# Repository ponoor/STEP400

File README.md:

# STEP400

STEP400 is a 4-axis stepper motor driver board with an Ethernet interface, designed for art installations, stage productions and exhibition machinery. It puts everything a typical motion setup needs onto one board:

- An Arduino Zero–compatible MCU (Microchip ATSAMD21G18A)
- Ethernet (WIZnet W5500)
- Four [STMicroelectronics powerSTEP01](https://www.st.com/en/motor-drivers/powerstep01.html) stepper drivers, supporting both voltage mode and current mode
- HOME and LIMIT sensor inputs for each axis
- A microSD card slot for loading the configuration file

The board is controlled with [Open Sound Control](https://opensoundcontrol.stanford.edu/) (OSC) over Ethernet, which works natively in Max, TouchDesigner, Processing, openFrameworks, Unity and other creative coding environments.

| | |
|---|---|
| Motor type | Bipolar stepper |
| Supply voltage | 12–72 V (absolute max. 80 V) |
| Max. phase current | 5 A |
| Microstepping | Up to 1/128 |
| PCB size | 120 × 84 mm |

STEP400 is part of the STEP series. Its sibling, [STEP800](https://github.com/ponoor/STEP800), drives eight smaller motors with L6470 drivers and shares the same firmware and OSC commands.

Friend of STEP400 : [STEP800](https://github.com/ponoor/STEP800)

## Store
https://ponoor.com/en/shop/

## Documentation
https://ponoor.com/en/docs/step-series/

Forum: https://github.com/ponoor/step-series-support/discussions

- **[STEP400/STEP800 documentation](https://ponoor.com/en/docs/step-series/)** ([日本語](https://ponoor.com/docs/step-series/))
  - [Tutorial](https://ponoor.com/en/docs/step-series/tutorial/)
  - [OSC command reference](https://ponoor.com/en/docs/step-series/osc-command-reference/)
  - [Hardware details](https://ponoor.com/en/docs/step-series/technical-information/hardware-step400/)
- [Electromagnetic brake board for STEP400](https://ponoor.com/en/docs/emb-step400/)
- Questions and support: [STEP series support forum](https://github.com/ponoor/step-series-support/discussions)

## Firmware

The firmware is maintained in a separate repository, shared with STEP800:

**[ponoor/step-series-universal-firmware](https://github.com/ponoor/step-series-universal-firmware)**

This repository used to contain the STEP400 firmware as well. Those directories have been removed, and the old releases here are no longer maintained. See [Firmware update](https://ponoor.com/en/docs/step-series/technical-information/firmware-update/) in the documentation for how to update a board.

## Repository contents

### `hardware/`

Design files for the current hardware revision (r1).

| File | Description |
|---|---|
| `step400_r1.sch`, `step400_r1.brd` | STEP400 r1 schematic and board (Autodesk EAGLE). These are the reference design files for r1. |
| `step400_r1_schematics.pdf` | STEP400 r1 schematic |
| `step400_r1_dimension.pdf` | Board dimensions and mounting holes |
| `step400_r1.0.1_BOM.csv` | Bill of materials for r1.0.1 (current) |
| `step400_r1.0.0_BOM.csv` | Bill of materials for r1.0.0 |
| `brakeBoard.sch`, `brakeBoard.brd` | Electromagnetic brake board (Autodesk EAGLE) |
| `brakeBoard_schematic.pdf`, `brakeBoard_BOM.csv` | Brake board schematic and bill of materials |
| `step400_r1/` | KiCad project imported from the EAGLE r1 files (see below) |

#### KiCad migration (work in progress)

We are moving the hardware design from EAGLE to KiCad for the next revision. `hardware/step400_r1/` holds the r1 design imported into KiCad 10, along with a footprint library (`step400_r1.pretty`) exported from the board.

The connectivity and footprints of this KiCad project have been checked against the EAGLE files. However, it is kept as a **reference for future work**, not as manufacturing data. The PCB still carries leftovers from the import (an unconsolidated layer stack, missing keepout areas, default design rules), so use the EAGLE files or the PDFs above if you need the exact r1 design.

### `configTool/`

Source of the web-based configuration tool, which creates the JSON configuration file that the board loads from its microSD card. A hosted version is available at [ponoor.com/tools/step400-config/](https://ponoor.com/tools/step400-config/). For usage, see [Setup with a microSD card](https://ponoor.com/en/docs/step-series/settings/setup-with-a-microsd-card/).

### `step400_hardware_tests/`

A PlatformIO project for the hardware inspection firmware, used to test assembled boards.

## Examples and libraries

| Environment | Repository |
|---|---|
| Max | [ponoor/step-series-example-Max](https://github.com/ponoor/step-series-example-Max) |
| TouchDesigner | [ponoor/step-series-example-TouchDesigner](https://github.com/ponoor/step-series-example-TouchDesigner) (by [@loveandsheep](https://github.com/loveandsheep)) |
| openFrameworks | [ponoor/step-series-example-openFrameworks](https://github.com/ponoor/step-series-example-openFrameworks) (by [@niimi](https://github.com/niimi)) |
| Unity | [ponoor/step-series-example-Unity](https://github.com/ponoor/step-series-example-Unity) (by [@niimi](https://github.com/niimi)) |
| Processing | [yuskegoto/STEP400_Processing](https://github.com/yuskegoto/STEP400_Processing) (by [@yuskegoto](https://github.com/yuskegoto)) |
| Node-RED | [yuskegoto/STEP400_Node-RED](https://github.com/yuskegoto/STEP400_Node-RED) (by [@yuskegoto](https://github.com/yuskegoto)) |
| Python | [ponoor/python-step-series](https://github.com/ponoor/python-step-series) |

## License

[MIT License](LICENSE) © Ponoor Experiments Inc.

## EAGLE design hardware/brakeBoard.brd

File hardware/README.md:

# Diagram
```mermaid
flowchart LR
	MCU ---|SPI/SERCOM4| W5500 --- Ethernet
	MCU --- |SPI/SERCOM3|PowerSTEP01 --> Motor
	HomeSw -->|SW| PowerSTEP01
	LimitSw -->|ADCIN| PowerSTEP01
	DIPSW --> MCU
	MCU --> Brake
  ```
  
  Check the [document](https://ponoor.com/en/docs/step-series/technical-information/hardware-step400/) for details.

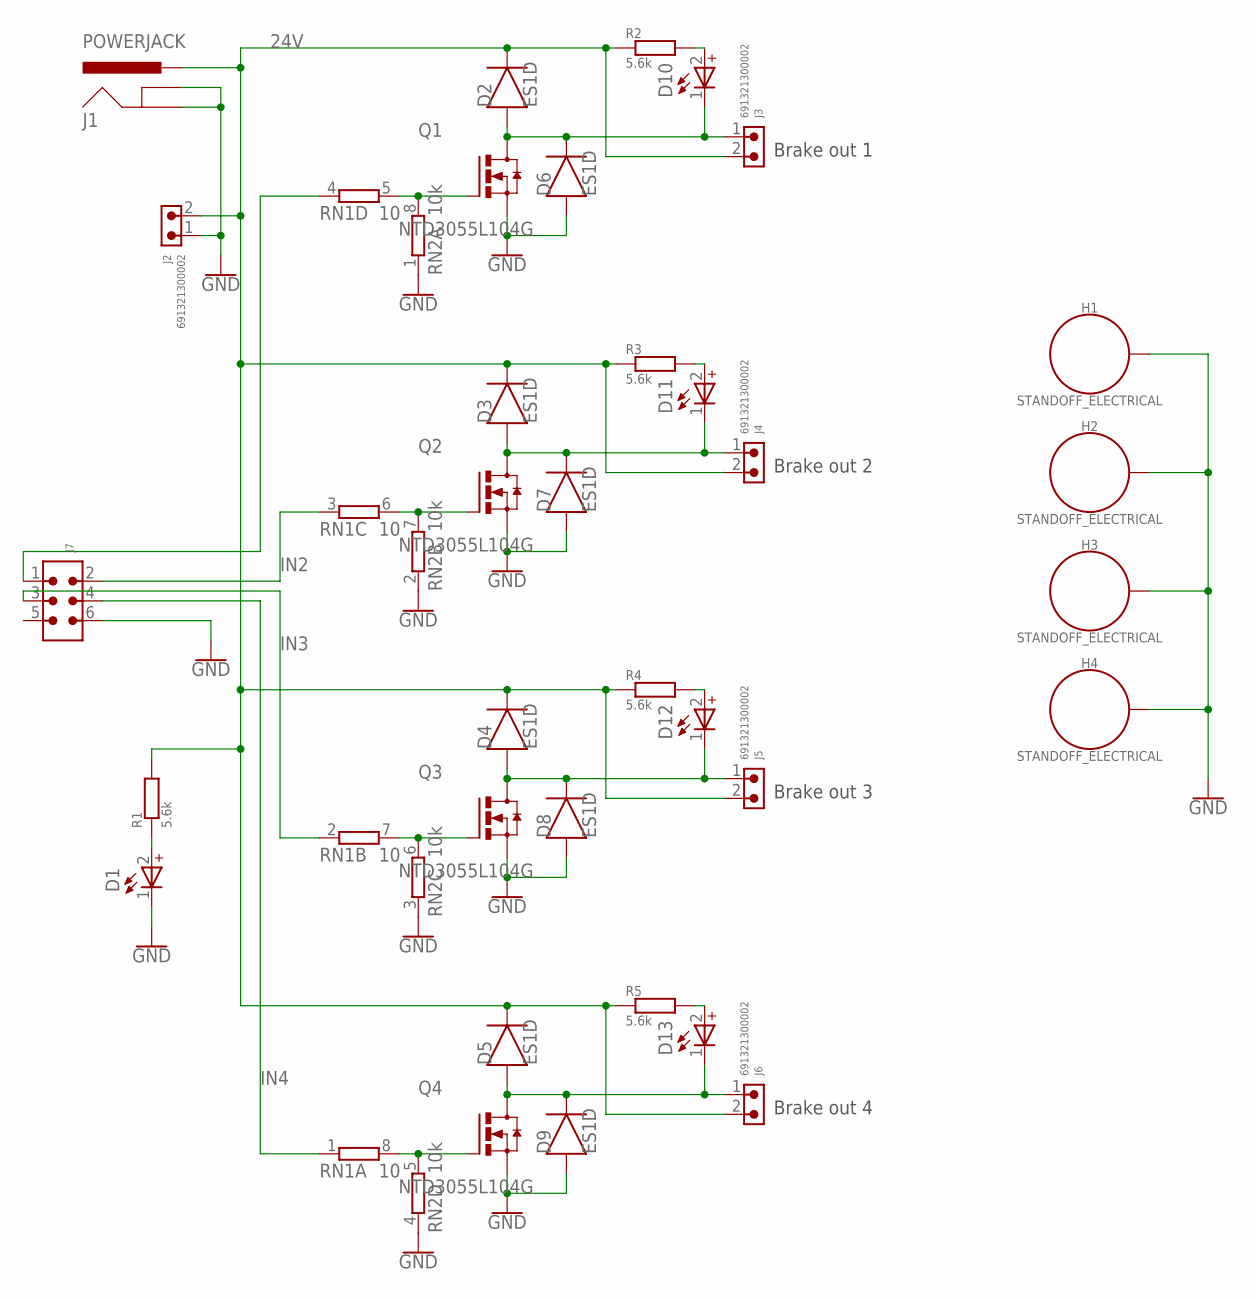
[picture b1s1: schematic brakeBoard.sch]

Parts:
D1, D10, D11, D12, D13: WL-SMCD_0603_150060GS55040; WL-SMCD_0603
D2, D3, D4, D5, D6, D7, D8, D9: ES1D; DIOM5226X290N
H1, H2, H3, H4: STANDOFF_ELECTRICAL; STANDOFF-ELECTRICAL
J1: POWERJACK; POWERJACK_SLOT
J2, J3, J4, J5, J6: 691321300002
J7: 6120XX21621_61200621621; 61200621621
Q1, Q2, Q3, Q4: NTD3055L104G; DPAK3
R1, R2, R3, R4, R5: 5.6k; RESC2012X65
RN1: 10; CAY16_LONG_W
RN2: 10k; CAY16_LONG_W

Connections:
24V: D2.1 (C), D3.1 (C), D4.1 (C), D5.1 (C), J1.P$2 (PWR), J1.P$3 (PWR), J1.P$4 (PWR), J1.P$5 (PWR), J1.P$6 (PWR), J1.P$7 (PWR), J1.P$8 (PWR), J1.P$9 (PWR), J1.P$10 (PWR), J1.P$11 (PWR), J1.P$12 (PWR), J1.P$13 (PWR), J1.P$14 (PWR), J1.P$15 (PWR), J1.P$16 (PWR), J1.P$17 (PWR), J1.P$18 (PWR), J1.P$19 (PWR), J1.P$20 (PWR), J1.P$21 (PWR), J1.P$22 (PWR), J1.P$23 (PWR), J1.P$24 (PWR), J1.P$25 (PWR), J1.P$26 (PWR), J1.P$27 (PWR), J1.P$28 (PWR), J2.2, J3.2, J4.2, J5.2, J6.2, R1.2, R2.1, R3.1, R4.1, R5.1
GND: D1.1 (_), D6.2 (A), D7.2 (A), D8.2 (A), D9.2 (A), H1.P1, H2.P1, H3.P1, H4.P1, J1.P$33 (GNDBREAK), J1.P$34 (GNDBREAK), J1.P$35 (GNDBREAK), J1.P$36 (GNDBREAK), J1.P$37 (GNDBREAK), J1.P$38 (GNDBREAK), J1.P$39 (GNDBREAK), J1.P$40 (GNDBREAK), J1.P$41 (GNDBREAK), J1.P$42 (GNDBREAK), J1.P$43 (GNDBREAK), J1.P$44 (GNDBREAK), J1.P$45 (GNDBREAK), J1.P$46 (GNDBREAK), J1.P$47 (GNDBREAK), J1.P$48 (GNDBREAK), J1.P$49 (GNDBREAK), J1.P$50 (GNDBREAK), J1.P$51 (GNDBREAK), J1.P$52 (GNDBREAK), J1.P$53 (GNDBREAK), J1.P$54 (GNDBREAK), J1.P$55 (GNDBREAK), J1.P$56 (GNDBREAK), J1.P$63 (GND), J1.P$64 (GND), J1.P$65 (GND), J1.P$66 (GND), J1.P$67 (GND), J1.P$68 (GND), J1.P$69 (GND), J1.P$70 (GND), J1.P$71 (GND), J1.P$72 (GND), J1.P$73 (GND), J1.P$74 (GND), J1.P$75 (GND), J1.P$76 (GND), J1.P$77 (GND), J1.P$78 (GND), J1.P$79 (GND), J1.P$80 (GND), J1.P$81 (GND), J1.P$82 (GND), J1.P$83 (GND), J1.P$84 (GND), J1.P$85 (GND), J2.1, J7.6, Q1.2 (S), Q2.2 (S), Q3.2 (S), Q4.2 (S), RN2.1, RN2.2 (1), RN2.3 (1), RN2.4 (1)
IN1: J7.1, RN1.4 (1)
IN2: J7.2, RN1.3 (1)
IN3: J7.3, RN1.2 (1)
IN4: J7.4, RN1.1
unnamed: D2.2 (A), D6.1 (C), D10.1 (_), J3.1, Q1.3 (D)
unnamed: D10.2 (+), R2.2
unnamed: Q1.1 (G), RN1.5 (2), RN2.8 (2)
unnamed: D3.2 (A), D7.1 (C), D11.1 (_), J4.1, Q2.3 (D)
unnamed: D11.2 (+), R3.2
unnamed: D4.2 (A), D8.1 (C), D12.1 (_), J5.1, Q3.3 (D)
unnamed: D12.2 (+), R4.2
unnamed: D5.2 (A), D9.1 (C), D13.1 (_), J6.1, Q4.3 (D)
unnamed: D13.2 (+), R5.2
unnamed: Q4.1 (G), RN1.8 (2), RN2.5 (2)
unnamed: Q3.1 (G), RN1.7 (2), RN2.6 (2)
unnamed: Q2.1 (G), RN1.6 (2), RN2.7 (2)
unnamed: D1.2 (+), R1.1

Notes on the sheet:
Brake out 1
Brake out 2
Brake out 3
Brake out 4

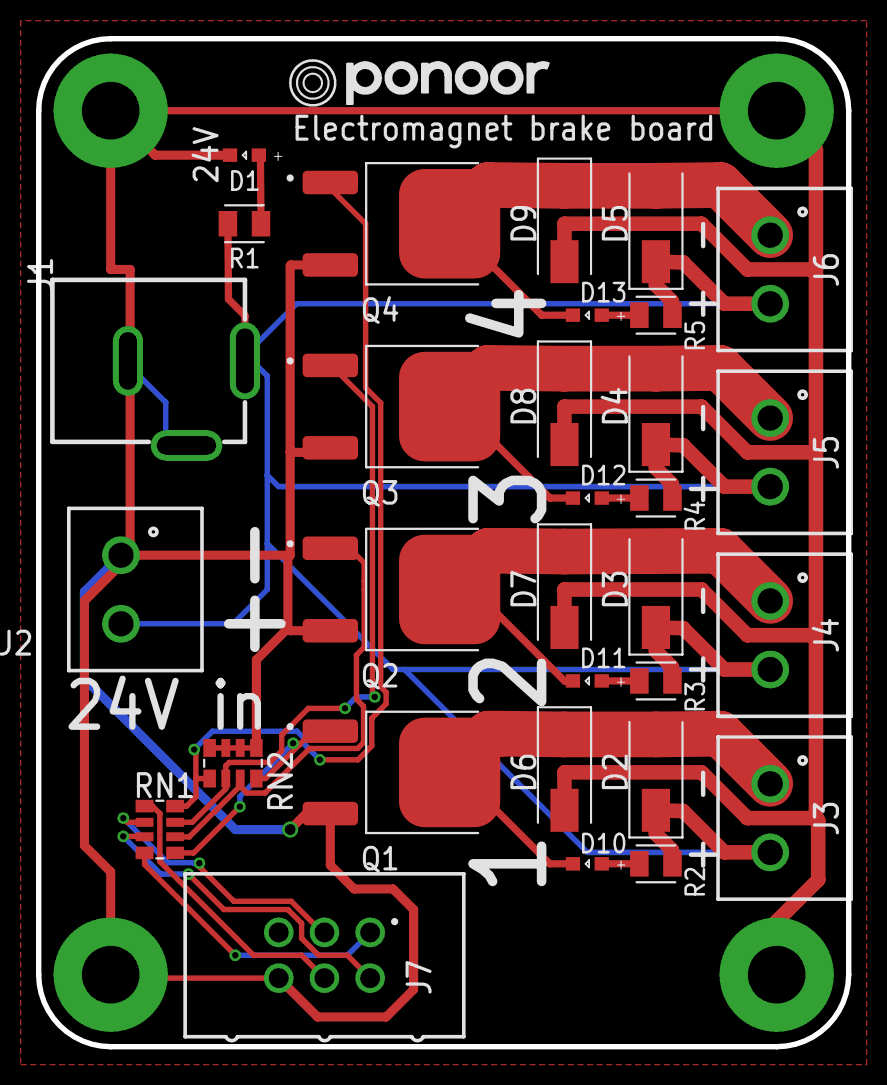
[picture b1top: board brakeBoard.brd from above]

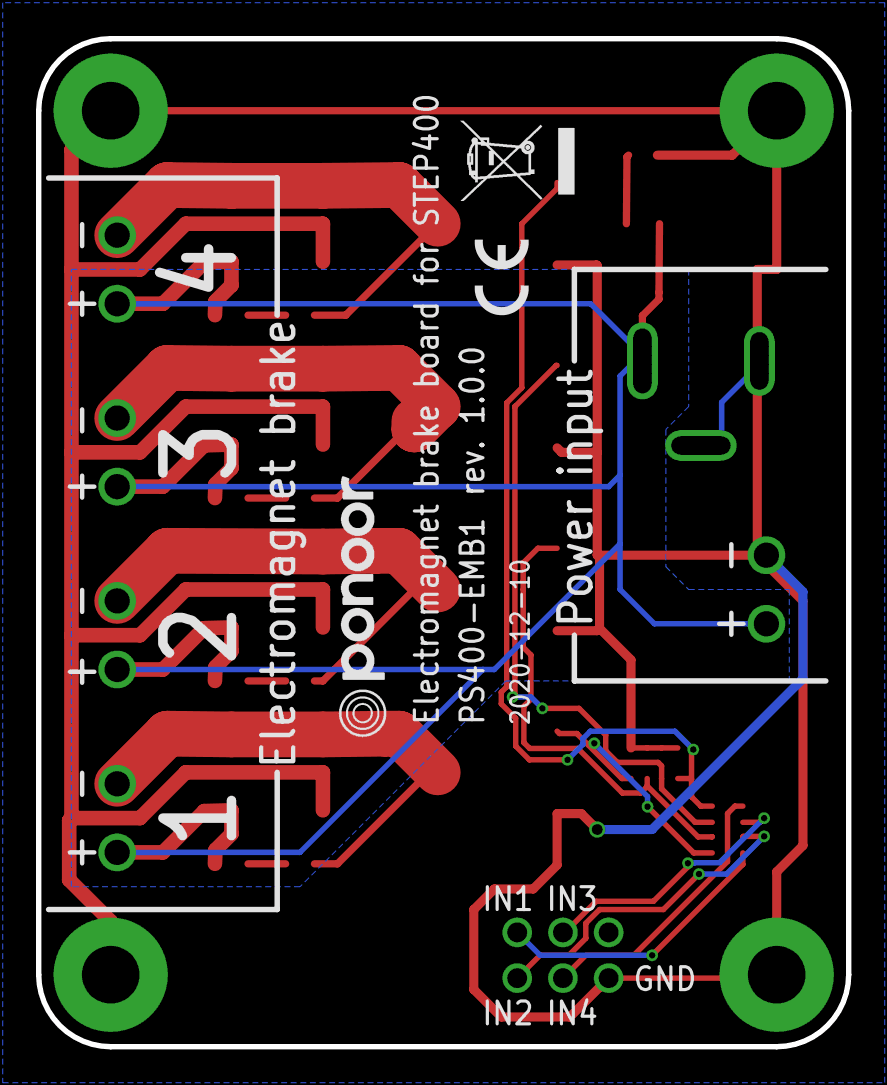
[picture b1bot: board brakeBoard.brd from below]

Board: 2 copper layers, 45.0 x 56.0 mm, 39 parts (3 on the bottom side), 19 nets.

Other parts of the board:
U$2, U$3: PONOOR_TEXT_15MM
U$5: WEEE_6MM
U$6: CE_3MM

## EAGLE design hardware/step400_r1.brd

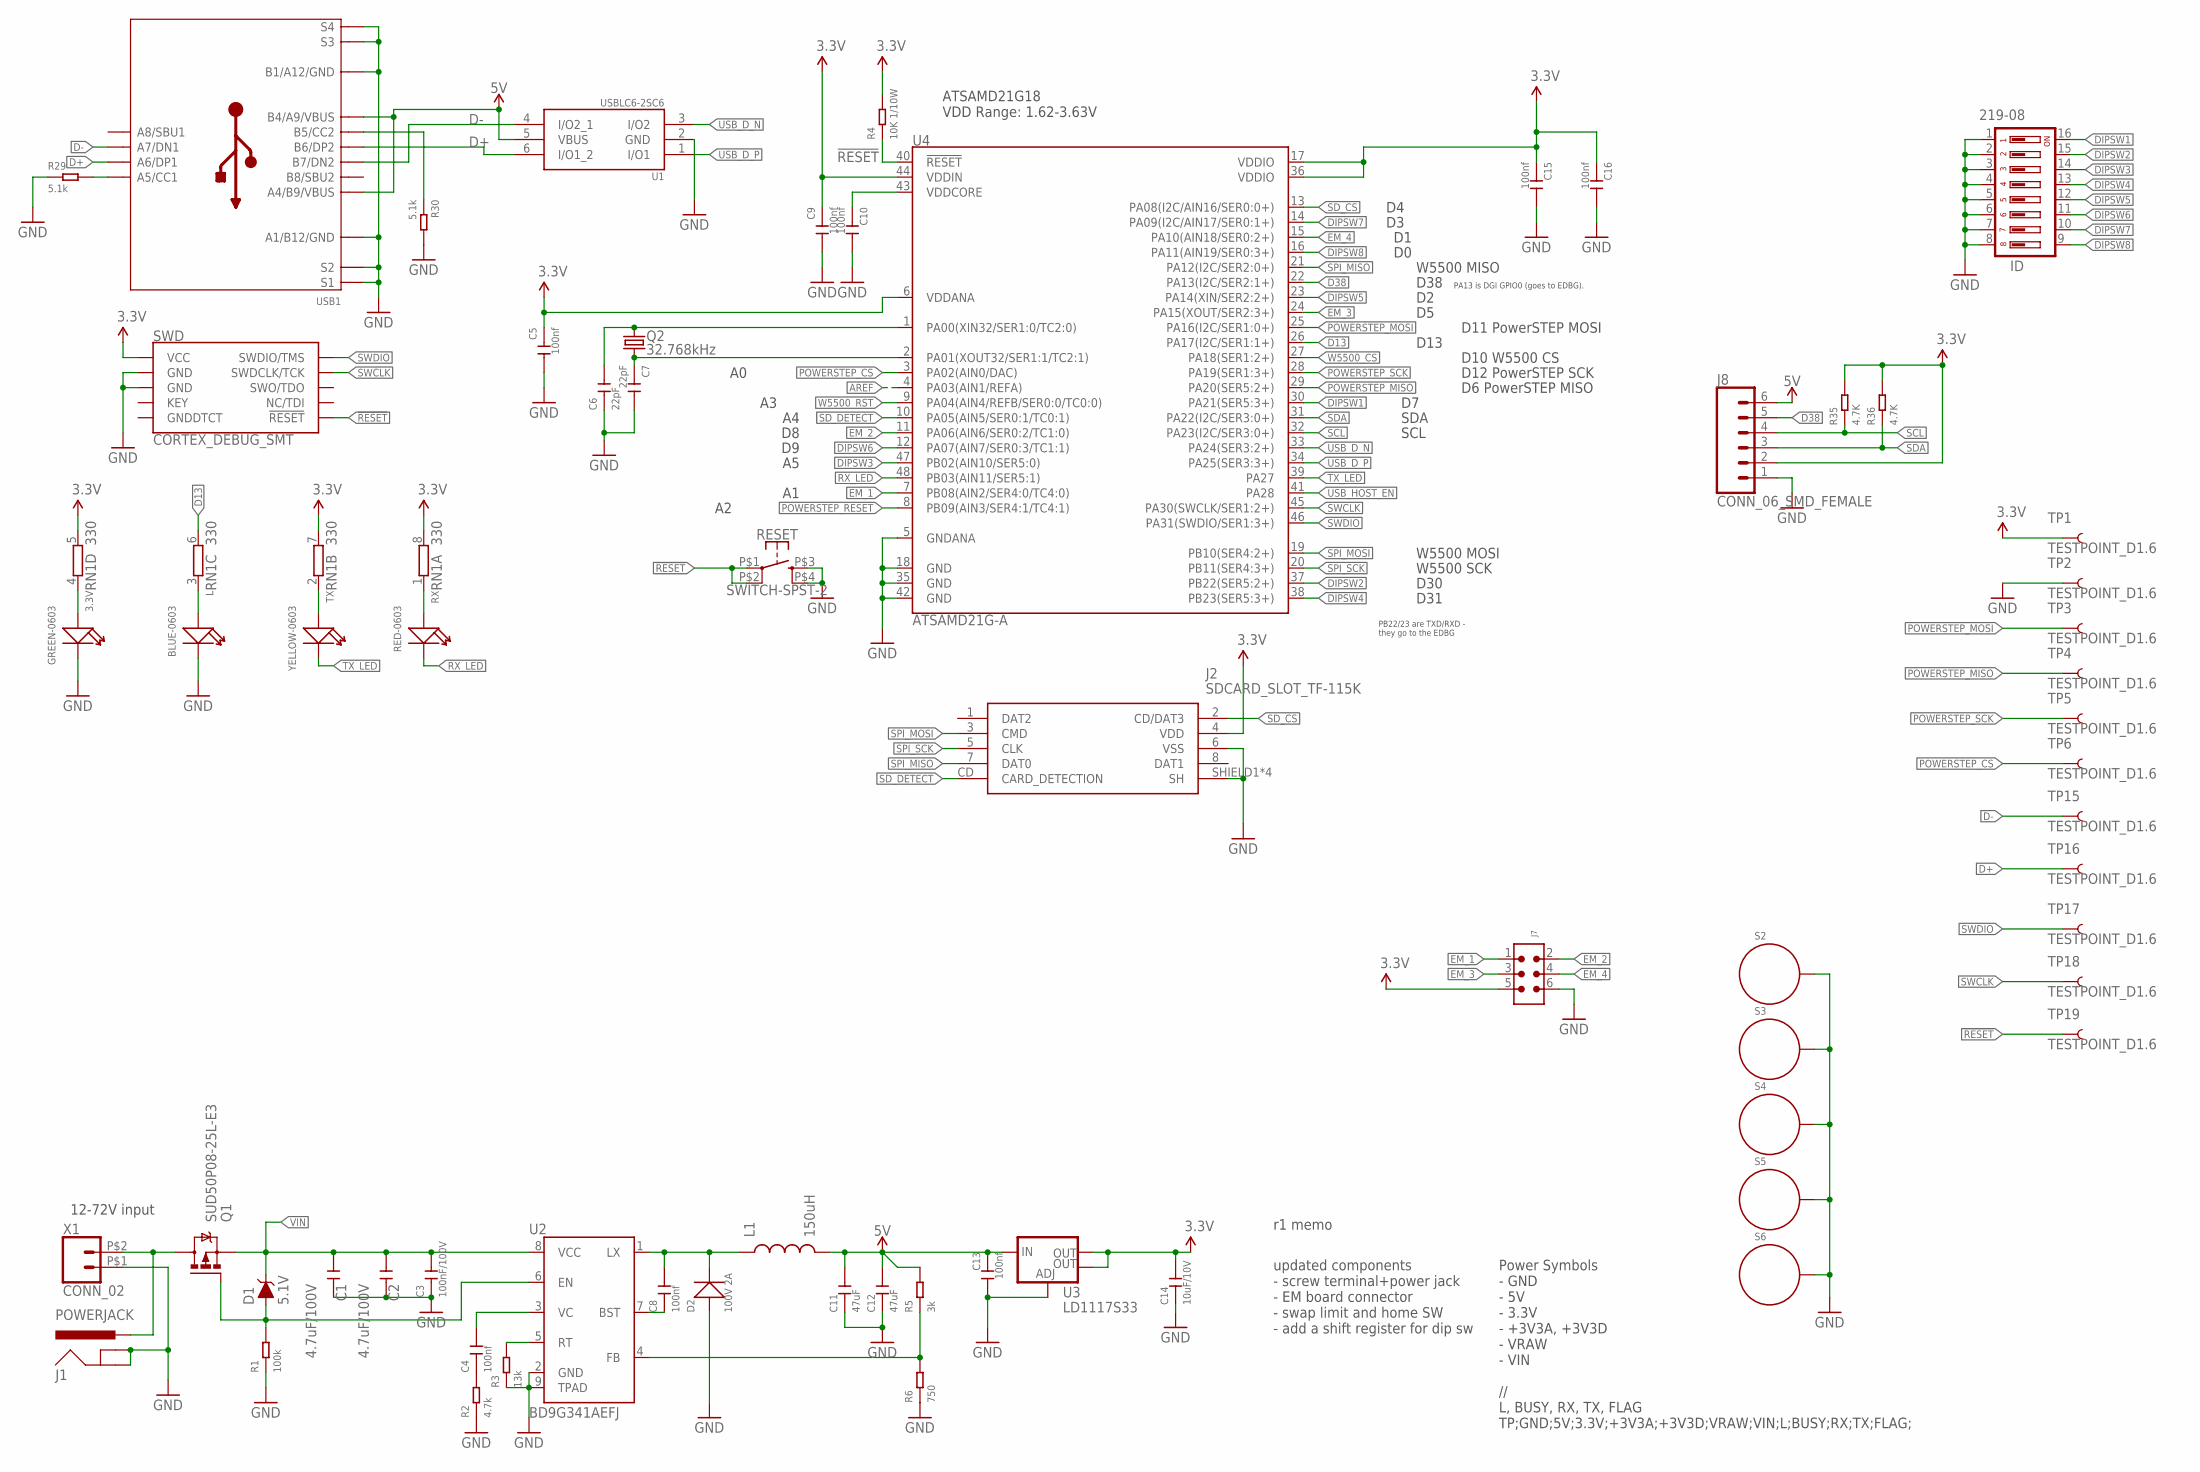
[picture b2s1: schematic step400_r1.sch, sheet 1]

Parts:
3.3V: GREEN-0603; LED-0603
C1, C2: 4.7uF/100V; C1210
C3: 100nF/100V; C0805
C4, C8: 100nf; C0603
C5, C9, C10, C13, C15, C16: 100nf; C0402
C6, C7: 22pF; C0402
C11, C12: 47uF; C1206
C14: 10uF/10V; C0805
D1: 5.1V; SOD-323
D2: 100V 2A; DO-214AC
ID: 219-08; CTS-219-08
J1: POWERJACK; POWERJACK_SLOT
J2: SDCARD_SLOT_TF-115K; TF-115K
J7: 6120XX21621_61200621621; 61200621621
J8: CONN_06_SMD_FEMALE; 1X06-SMD-FEMALE
L: BLUE-0603; LED-0603
L1: 150uH; L5045_L
Q1: SUD50P08-25L-E3; D-PAK_TO252AA
Q2: 32.768kHz; FC-135
R1: 100k; R0603
R2: 4.7k; R0603
R3: 13k; R0603
R4: 10K 1/10W; R0603
R5: 3k; R0603
R6: 750; R0603
R29, R30: 5.1k; R0603
R35, R36: 4.7K; R0603
RESET: SWITCH-SPST-2; SKRP
RN1: 330; CAY16_LONG_W
RX: RED-0603; LED-0603
S2, S3, S4, S5, S6: STANDOFF_ELECTRICAL; STANDOFF-ELECTRICAL
SWD: CORTEX_DEBUG_SMT; 20021121-00010C4LF
TP1, TP2, TP3, TP4, TP5, TP6, TP15, TP16, TP17, TP18, TP19: TESTPOINT_D1.6
TX: YELLOW-0603; LED-0603
U1: USBLC6-2SC6; SOT23-6L
U2: BD9G341AEFJ; SOIC127P600X100-9N
U3: LD1117S33; SOT223
U4: ATSAMD21G-A; TQFP-48
USB1: USB-C_USB2.0-TYPE-C
X1: CONN_02; WJ25C-B-7.62-2P

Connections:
3.3V: C5.1, C9.1, C14.2, C15.1, C16.1, J2.4 (VDD), J7.5, J8.2, R4.2, R35.2, R36.2, RN1.5 (2), RN1.7 (2), RN1.8 (2), SWD.P$1 (VCC), TP1.1, U3.2 (OUT), U3.4 (OUT), U4.6 (VDDANA), U4.17 (VDDIO), U4.36 (VDDIO), U4.44 (VDDIN); also elsewhere on the board
5V: C11.2, C12.2, C13.1, J8.6, L1.P$2 (2), R5.2, U1.5 (VBUS), U3.3 (IN), USB1.A4_B9 (A4/B9/VBUS), USB1.B4_A9 (B4/A9/VBUS); also elsewhere on the board
!RESET: R4.1, RESET.P$1 (1), RESET.P$2 (2), SWD.P$10 (!RESET), TP19.1, U4.40 (!RESET!)
AREF: U4.4 (PA03(AIN1/REFA))
D13: RN1.6 (2), U4.26 (PA17(I2C/SER1:1+))
D38: J8.5, U4.22 (PA13(I2C/SER2:1+))
D+: TP16.1, U1.6 (I/O1_2), USB1.A6 (A6/DP1), USB1.B6 (B6/DP2)
D-: TP15.1, U1.4 (I/O2_1), USB1.A7 (A7/DN1), USB1.B7 (B7/DN2)
DIPSW1: ID.16, U4.30 (PA21(SER5:3+))
DIPSW2: ID.15, U4.37 (PB22(SER5:2+))
DIPSW3: ID.14, U4.47 (PB02(AIN10/SER5:0))
DIPSW4: ID.13, U4.38 (PB23(SER5:3+))
DIPSW5: ID.12, U4.23 (PA14(XIN/SER2:2+))
DIPSW6: ID.11, U4.12 (PA07(AIN7/SER0:3/TC1:1))
DIPSW7: ID.10, U4.14 (PA09(I2C/AIN17/SER0:1+))
DIPSW8: ID.9, U4.16 (PA11(AIN19/SER0:3+))
EM_1: J7.1, U4.7 (PB08(AIN2/SER4:0/TC4:0))
EM_2: J7.2, U4.11 (PA06(AIN6/SER0:2/TC1:0))
EM_3: J7.3, U4.24 (PA15(XOUT/SER2:3+))
EM_4: J7.4, U4.15 (PA10(AIN18/SER0:2+))
GND: 3.3V.-, C1.2, C2.2, C3.1, C5.2, C6.1, C7.2, C9.2, C10.2, C11.1, C12.1, C13.2, C14.1, C15.2, C16.2, D2.1 (+), ID.1, ID.2, ID.3, ID.4, ID.5, ID.6, ID.7, ID.8, J1.P$33 (GNDBREAK), J1.P$34 (GNDBREAK), J1.P$35 (GNDBREAK), J1.P$36 (GNDBREAK), J1.P$37 (GNDBREAK), J1.P$38 (GNDBREAK), J1.P$39 (GNDBREAK), J1.P$40 (GNDBREAK), J1.P$41 (GNDBREAK), J1.P$42 (GNDBREAK), J1.P$43 (GNDBREAK), J1.P$44 (GNDBREAK), J1.P$45 (GNDBREAK), J1.P$46 (GNDBREAK), J1.P$47 (GNDBREAK), J1.P$48 (GNDBREAK), J1.P$49 (GNDBREAK), J1.P$50 (GNDBREAK), J1.P$51 (GNDBREAK), J1.P$52 (GNDBREAK), J1.P$53 (GNDBREAK), J1.P$54 (GNDBREAK), J1.P$55 (GNDBREAK), J1.P$56 (GNDBREAK), J1.P$63 (GND), J1.P$64 (GND), J1.P$65 (GND), J1.P$66 (GND), J1.P$67 (GND), J1.P$68 (GND), J1.P$69 (GND), J1.P$70 (GND), J1.P$71 (GND), J1.P$72 (GND), J1.P$73 (GND), J1.P$74 (GND), J1.P$75 (GND), J1.P$76 (GND), J1.P$77 (GND), J1.P$78 (GND), J1.P$79 (GND), J1.P$80 (GND), J1.P$81 (GND), J1.P$82 (GND), J1.P$83 (GND), J1.P$84 (GND), J1.P$85 (GND), J2.6 (VSS), J2.SHIELD1 (SH), J2.SHIELD2 (SH), J2.SHIELD3 (SH), J2.SHIELD4 (SH), J7.6, J8.1, L.-, R1.1, R2.1, R3.1, R6.1, R29.1, R30.2, RESET.P$3 (3), RESET.P$4 (4), S2.P1, S3.P1, S4.P1, S5.P1, S6.P1, SWD.P$3 (GND), SWD.P$5 (GND), TP2.1, U1.2 (GND), U2.2 (GND), U2.9 (TPAD), U3.1 (ADJ), U4.5 (GNDANA), U4.18 (GND), U4.35 (GND), U4.42 (GND), USB1.A1_B12 (A1/B12/GND), USB1.B1_A12 (B1/A12/GND), USB1.S7 (S1), USB1.S8 (S1), USB1.S9 (S1), USB1.S10 (S1), USB1.S11 (S1), USB1.S12 (S1), USB1.S13 (S1), USB1.S14 (S1), USB1.S15 (S1), USB1.S16 (S3), USB1.S17 (S3), USB1.S18 (S3), USB1.S19 (S3), USB1.S20 (S3), USB1.S21 (S3), USB1.S22 (S3), USB1.S23 (S3), USB1.S24 (S3), USB1.S25 (S3), USB1.S26 (S3), USB1.S27 (S3), USB1.S29 (S2), USB1.S30 (S2), USB1.S31 (S2), USB1.S32 (S2), USB1.S33 (S2), USB1.S34 (S2), USB1.S35 (S2), USB1.S36 (S2), USB1.S37 (S4), USB1.S38 (S4), USB1.S39 (S4), USB1.S40 (S4), USB1.S41 (S4), USB1.S42 (S4), USB1.S43 (S4), USB1.S44 (S4), USB1.S45 (S4), USB1.S46 (S4), USB1.S47 (S4), USB1.S48 (S4), X1.P$1 (1); also elsewhere on the board
unnamed: C6.2, Q2.P$2 (2), U4.1 (PA00(XIN32/SER1:0/TC2:0))
unnamed: C4.1, R2.2
unnamed: C7.1, Q2.P$1 (1), U4.2 (PA01(XOUT32/SER1:1/TC2:1))
unnamed: RN1.1, RX.+
unnamed: RN1.2 (1), TX.+
unnamed: R5.1, R6.2, U2.4 (FB)
unnamed: D1.A, Q1.1 (G), R1.2, U2.6 (EN)
unnamed: R3.2, U2.5 (RT)
unnamed: L.+, RN1.3 (1)
unnamed: 3.3V.+, RN1.4 (1)
unnamed: C4.2, U2.3 (VC)
unnamed: C8.1, U2.7 (BST)
unnamed: C8.2, D2.2 (-), L1.P$1 (1), U2.1 (LX)
unnamed: R30.1, USB1.B5 (B5/CC2)
unnamed: R29.2, USB1.A5 (A5/CC1)
POWERSTEP_CS: TP6.1, U4.3 (PA02(AIN0/DAC)); also elsewhere on the board
POWERSTEP_MISO: TP4.1, U4.29 (PA20(SER5:2+)); also elsewhere on the board
POWERSTEP_MOSI: TP3.1, U4.25 (PA16(I2C/SER1:0+)); also elsewhere on the board
POWERSTEP_RESET: U4.8 (PB09(AIN3/SER4:1/TC4:1)); also elsewhere on the board
POWERSTEP_SCK: TP5.1, U4.28 (PA19(SER1:3+)); also elsewhere on the board
RX_LED: RX.-, U4.48 (PB03(AIN11/SER5:1))
SCL: J8.4, R35.1, U4.32 (PA23(I2C/SER3:0+))
SDA: J8.3, R36.1, U4.31 (PA22(I2C/SER3:0+))
SD_CS: J2.2 (CD/DAT3), U4.13 (PA08(I2C/AIN16/SER0:0+))
SD_DETECT: J2.CD (CARD_DETECTION), U4.10 (PA05(AIN5/SER0:1/TC0:1))
SPI_MISO: J2.7 (DAT0), U4.21 (PA12(I2C/SER2:0+)); also elsewhere on the board
SPI_MOSI: J2.3 (CMD), U4.19 (PB10(SER4:2+)); also elsewhere on the board
SPI_SCK: J2.5 (CLK), U4.20 (PB11(SER4:3+)); also elsewhere on the board
SWCLK: SWD.P$4 (SWDCLK/TCK), TP18.1, U4.45 (PA30(SWCLK/SER1:2+))
SWDIO: SWD.P$2 (SWDIO/TMS), TP17.1, U4.46 (PA31(SWDIO/SER1:3+))
TX_LED: TX.-, U4.39 (PA27)
USB_D_N: U1.3 (I/O2), U4.33 (PA24(SER3:2+))
USB_D_P: U1.1 (I/O1), U4.34 (PA25(SER3:3+))
USB_HOST_EN: U4.41 (PA28)
VDDCORE: C10.1, U4.43 (VDDCORE)
VIN: C1.1, C2.1, C3.2, D1.C, Q1.3 (S), U2.8 (VCC); also elsewhere on the board
VRAW: J1.P$2 (PWR), J1.P$3 (PWR), J1.P$4 (PWR), J1.P$5 (PWR), J1.P$6 (PWR), J1.P$7 (PWR), J1.P$8 (PWR), J1.P$9 (PWR), J1.P$10 (PWR), J1.P$11 (PWR), J1.P$12 (PWR), J1.P$13 (PWR), J1.P$14 (PWR), J1.P$15 (PWR), J1.P$16 (PWR), J1.P$17 (PWR), J1.P$18 (PWR), J1.P$19 (PWR), J1.P$20 (PWR), J1.P$21 (PWR), J1.P$22 (PWR), J1.P$23 (PWR), J1.P$24 (PWR), J1.P$25 (PWR), J1.P$26 (PWR), J1.P$27 (PWR), J1.P$28 (PWR), Q1.4 (D), X1.P$2 (2)
W5500_CS: U4.27 (PA18(SER1:2+)); also elsewhere on the board
W5500_RST: U4.9 (PA04(AIN4/REFB/SER0:0/TC0:0)); also elsewhere on the board

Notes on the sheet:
PB22/23 are TXD/RXD - they go to the EDBG
PA13 is DGI GPIO0 (goes to EDBG).
ATSAMD21G18 VDD Range: 1.62-3.63V
D30
D12 PowerSTEP SCK
D10 W5500 CS
D11 PowerSTEP MOSI
D13
D6 PowerSTEP MISO
D38
12-72V input
W5500 MISO
W5500 MOSI
W5500 SCK
SDA
SCL
D31
r1 memo
updated components - screw terminal+power jack - EM board connector - swap limit and home SW - add a shift register for dip sw
Power Symbols - GND - 5V - 3.3V - +3V3A, +3V3D - VRAW - VIN // L, BUSY, RX, TX, FLAG TP;GND;5V;3.3V;+3V3A;+3V3D;VRAW;VIN;L;BUSY;RX;TX;FLAG;

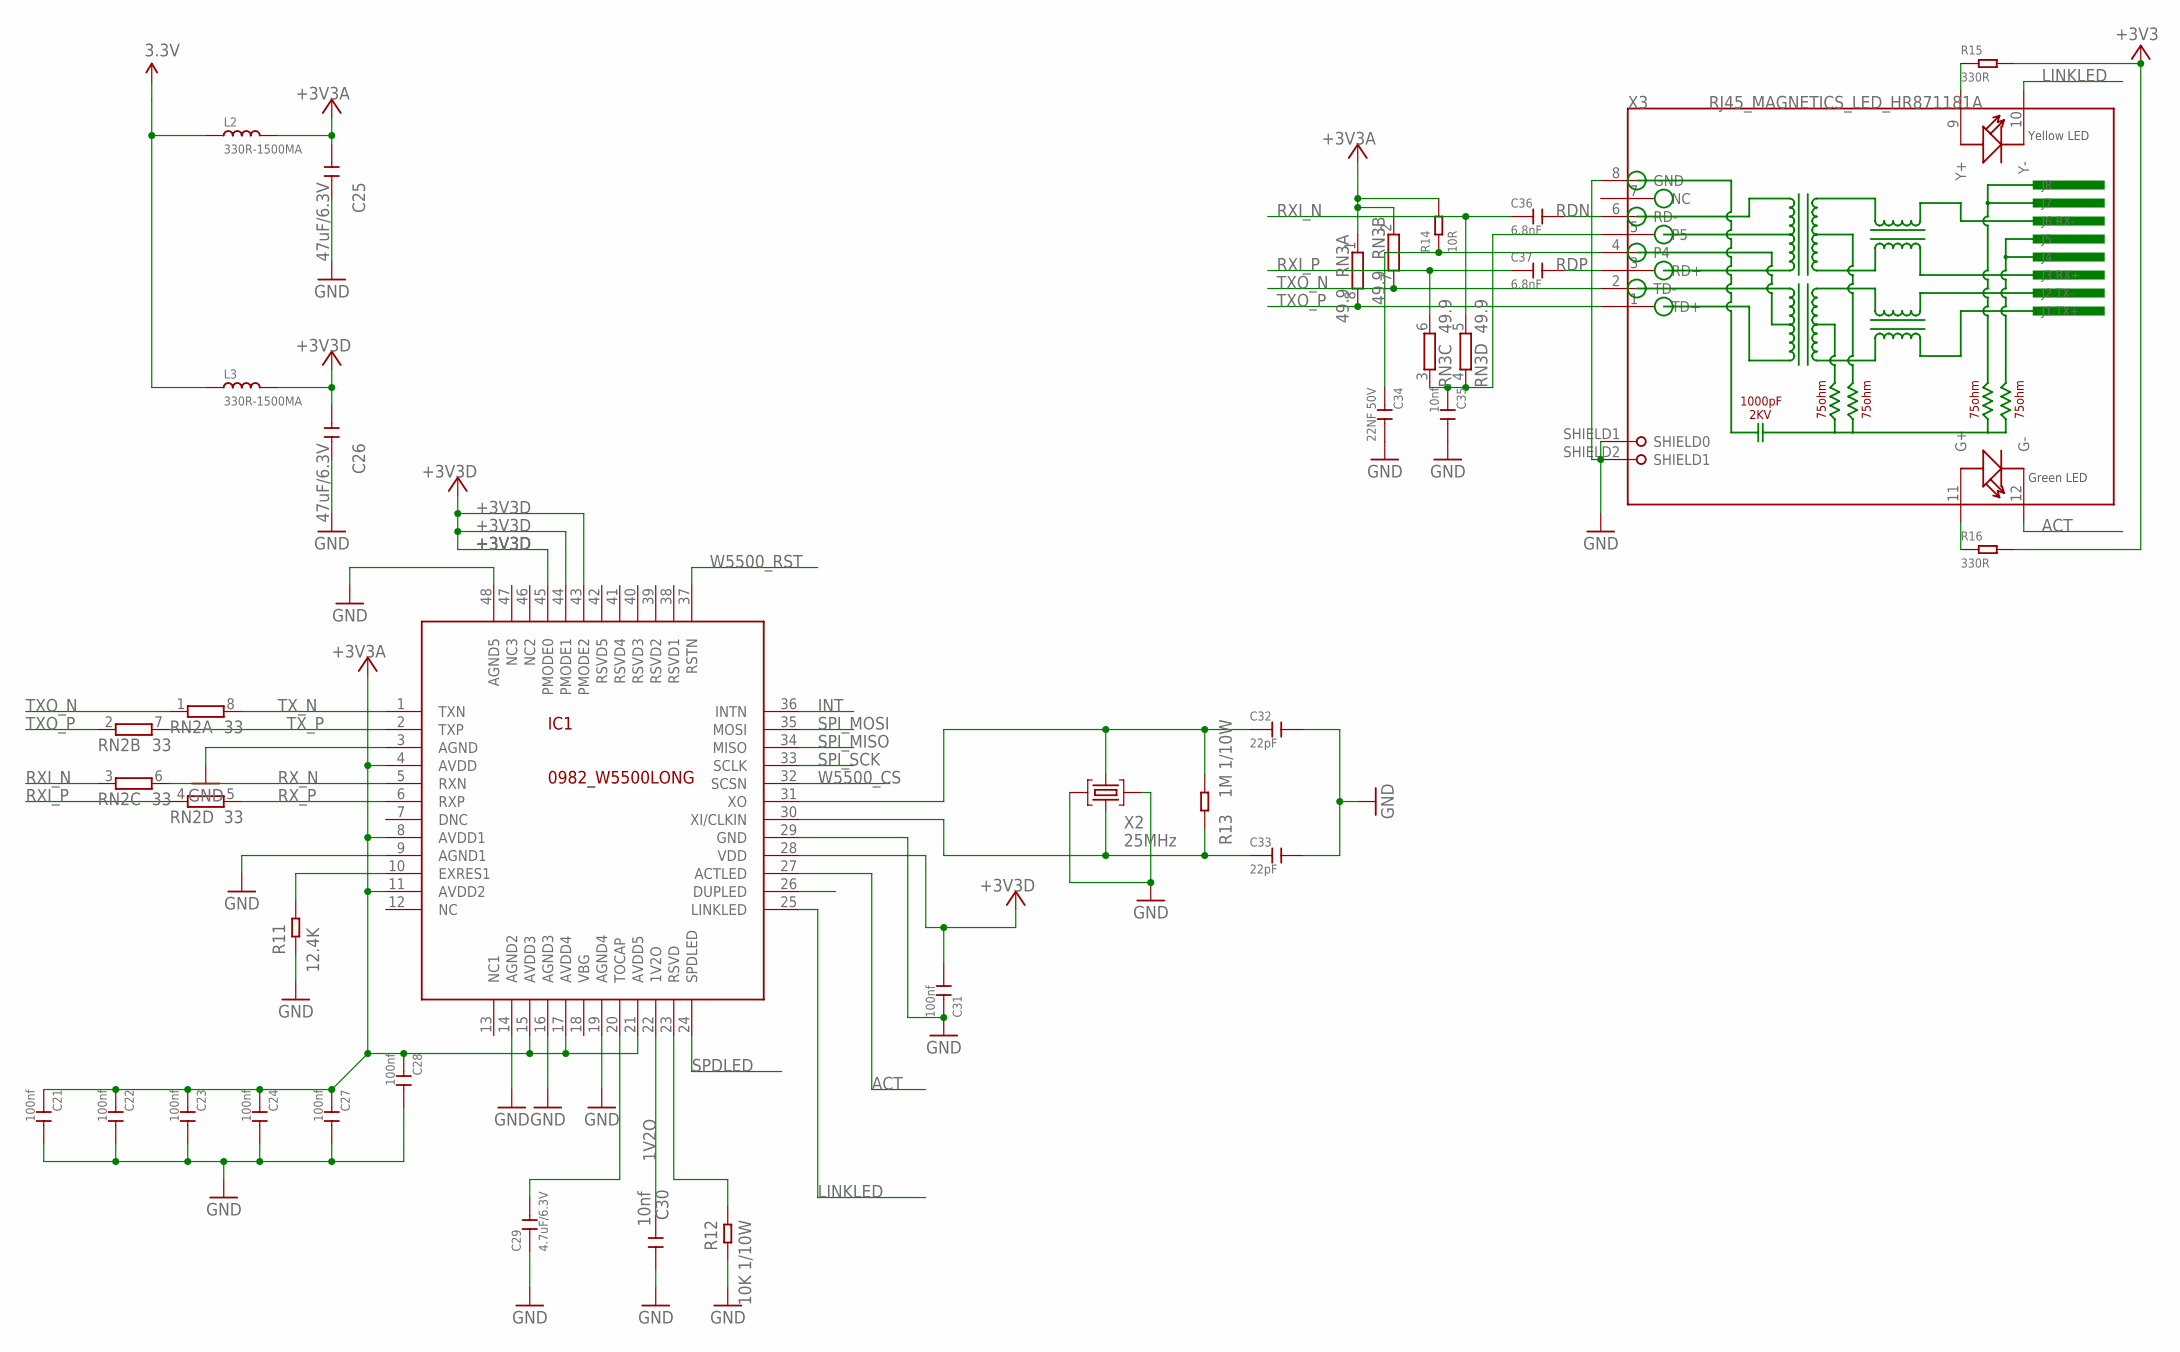
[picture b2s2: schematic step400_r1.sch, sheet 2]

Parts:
C21, C22, C23, C24, C27, C28, C31: 100nf; C0402
C25, C26: 47uF/6.3V; C1206
C29: 4.7uF/6.3V; C0603
C30, C35: 10nf; C0402
C32, C33: 22pF; C0402
C34: 22NF 50V; C0402
C36, C37: 6.8nF; C0402
IC1: 0982_W5500LONG; TQFP48-LONG
L2, L3: 330R-1500MA; L0805
R11: 12.4K; R0603
R12: 10K 1/10W; R0603
R13: 1M 1/10W; R0603
R14: 10R; R0603
R15, R16: 330R; R0603
RN2: 33; CAY16_LONG_W
RN3: 49.9; CAY16_LONG_W
X2: 25MHz; CRYSTAL-3.2-2.5
X3: RJ45_MAGNETICS_LED_HR871181A; HR871181A

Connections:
1V2O: C30.2, IC1.22 (1V2O)
3.3V: L2.1, L3.1, R15.2, R16.2; also elsewhere on the board
+3V3A: C21.1, C22.1, C23.1, C24.1, C25.1, C27.1, C28.1, IC1.4 (AVDD), IC1.8 (AVDD1), IC1.11 (AVDD2), IC1.15 (AVDD3), IC1.17 (AVDD4), IC1.21 (AVDD5), L2.2, R14.2, RN3.1, RN3.2 (1)
+3V3D: C26.1, C31.2, IC1.28 (VDD), IC1.43 (PMODE2), IC1.44 (PMODE1), IC1.45 (PMODE0), L3.2
ACT: IC1.27 (ACTLED), X3.12 (G-)
FDXLED: IC1.26 (DUPLED)
GND: C21.2, C22.2, C23.2, C24.2, C25.2, C26.2, C27.2, C28.2, C29.1, C30.1, C31.1, C32.2, C33.2, C34.2, C35.2, IC1.3 (AGND), IC1.9 (AGND1), IC1.14 (AGND2), IC1.16 (AGND3), IC1.19 (AGND4), IC1.29 (GND), IC1.48 (AGND5), R11.1, R12.1, X2.2 (GND), X2.4 (GND), X3.8 (GND), X3.SHIELD1 (SHIELD0), X3.SHIELD2 (SHIELD1); also elsewhere on the board
INT: IC1.36 (INTN)
LINKLED: IC1.25 (LINKLED), X3.10 (Y-)
unnamed: C32.1, IC1.31 (XO), R13.1, X2.3 (C2)
unnamed: C34.1, R14.1, X3.4
unnamed: C35.1, RN3.3 (1), RN3.4 (1), X3.5
unnamed: R15.1, X3.9 (Y+)
unnamed: R16.1, X3.11 (G+)
unnamed: IC1.23 (RSVD), R12.2
unnamed: C29.2, IC1.20 (TOCAP)
unnamed: IC1.10 (EXRES1), R11.2
NC: IC1.12 (NC)
OSC2E2: C33.1, IC1.30 (XI/CLKIN), R13.2, X2.1 (C1)
RDN: C36.2, X3.6 (RD-)
RDP: C37.2, X3.3 (RD+)
RSVD1: IC1.38 (RSVD1)
RSVD2: IC1.39 (RSVD2)
RSVD3: IC1.40 (RSVD3)
RXI_N: C36.1, RN2.3 (1), RN3.5 (2)
RXI_P: C37.1, RN2.4 (1), RN3.6 (2)
RX_N: IC1.5 (RXN), RN2.6 (2)
RX_P: IC1.6 (RXP), RN2.5 (2)
SPDLED: IC1.24 (SPDLED)
SPI_MISO: IC1.34 (MISO); also elsewhere on the board
SPI_MOSI: IC1.35 (MOSI); also elsewhere on the board
SPI_SCK: IC1.33 (SCLK); also elsewhere on the board
TXO_N: RN2.1, RN3.7 (2), X3.2 (TD-)
TXO_P: RN2.2 (1), RN3.8 (2), X3.1 (TD+)
TX_N: IC1.1 (TXN), RN2.8 (2)
TX_P: IC1.2 (TXP), RN2.7 (2)
W5500_CS: IC1.32 (SCSN); also elsewhere on the board
W5500_RST: IC1.37 (RSTN); also elsewhere on the board

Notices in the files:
parts and their libraries:
Wurth_LEDs_WL-SMCD: Copyright: Würth Elektronik
SparkFun-Hardware: Licensing: Creative Commons ShareAlike 4.0 International - https://creativecommons.org/licenses/by-sa/4.0
